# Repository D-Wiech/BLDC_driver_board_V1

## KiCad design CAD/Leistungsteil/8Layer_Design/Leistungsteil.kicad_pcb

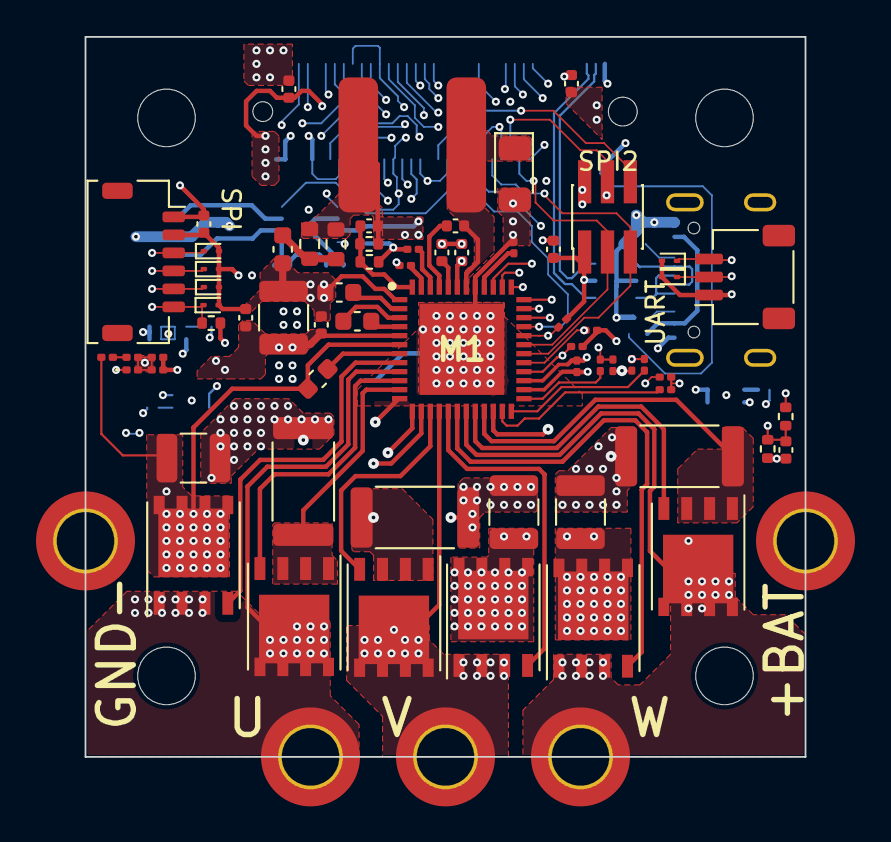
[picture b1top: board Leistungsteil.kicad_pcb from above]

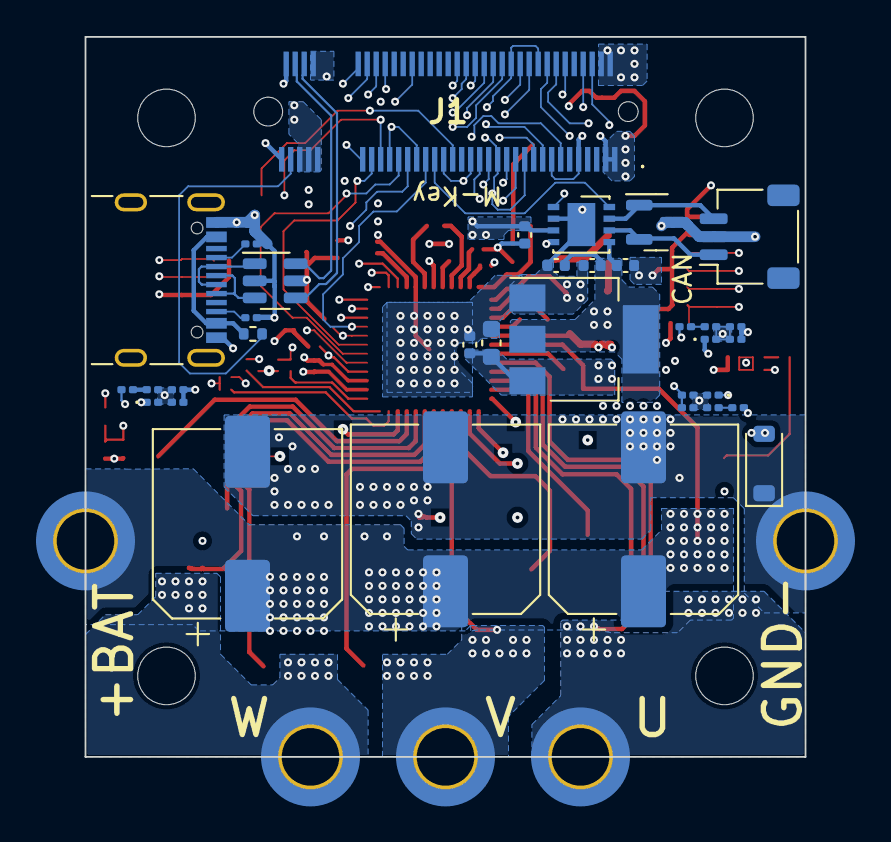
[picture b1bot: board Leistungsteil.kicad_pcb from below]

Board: 8 copper layers, 40.0 x 40.0 mm, 109 parts (35 on the bottom side), 75 nets.

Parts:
CAN_Con1, CAN_Con2: Conn_01x03_Pin; JST_SH_SM03B-SRSS-TB_1x03-1MP_P1.00mm_Horizontal
C_1: 10u; C_1210_3225Metric
C_5V1: 10u; C_0603_1608Metric
C_BST1: 10n; C_0402_1005Metric
C_DVDD1: 1u; C_0201_0603Metric
C_DVDD2: 1u; C_0603_1608Metric
C_FB1: 1n6; C_0402_1005Metric
C_Filter_U1: 1n; C_0201_0603Metric
C_Filter_V1: 1n; C_0201_0603Metric
C_Filter_W1: 1n; C_0201_0603Metric
C_IN1, C_IN2, C_IN3: 100u; CP_Elec_10x10
C_IN4, C_IN5, C_IN6: 10u; C_1210_3225Metric
C_IN7: 100n; C_0402_1005Metric
C_LDO1, C_LDO2, C_LDO6: 22u; C_0402_1005Metric
C_LDO3: 10u; C_0603_1608Metric
C_LDO4, C_LDO5: 100n; C_0402_1005Metric
C_PUMP1: 47n; C_0603_1608Metric
C_Reset1, C_Reset2: 100n; C_0402_1005Metric
C_SENS_Temp1: 100n; C_0402_1005Metric
C_SPI1, C_SPI2: 100n; C_0402_1005Metric
C_VCC1: 470n; C_0402_1005Metric
C_VDRAIN1: 1u; C_0603_1608Metric
C_VM1, C_VM2: 100n; C_0402_1005Metric
C_VM_1: 100n; C_0201_0603Metric
C_Vref1: 1u; C_0201_0603Metric
C_sense_U1: 10n; C_0201_0603Metric
C_sense_V1: 10n; C_0201_0603Metric
C_sense_W1: 10n; C_0201_0603Metric
D1: FES1DE; DO-219AA
D1_ESD1, D1_ESD2, D1_ESD3, D1_ESD4, D1_ESD5, D1_ESD6: ESD9B3.3ST5G; D_SOD-923
D2: PESD1CAN; SOT-23
D_TVS1: SMF54CA; D_SOD-123
D_VBAT1: RB751S-40DP-TP; D_0201_0603Metric
D_sense_U1: RB751S-40DP-TP; D_0201_0603Metric
D_sense_V1: RB751S-40DP-TP; D_0201_0603Metric
D_sense_W1: RB751S-40DP-TP; D_0201_0603Metric
H1, H2, H3, H4: MountingHole; MountingHole_3.2mm_M3_DIN965
J1: Bus_M.2_Socket_M; APCI0110
J7: USB_C_Receptacle_USB2.0; USB_C_Receptacle_GCT_USB4105-xx-A_16P_TopMnt_Horizontal
JST_SPI1: Conn_01x06_Female; JST_SHL_SM06B-SHLS-TF_1x06-1MP_P1.00mm_Horizontal
L1: 470u; NRSE8040-471M
M1: DRV8353RSRGZR; QFN50P700X700X100-49N-D
NTC1: 10k; R_0402_1005Metric
Negativ1: MountingHole_Pad; MountingHole_3.2mm_M3_ISO14580_Pad_TopBottom
Phase_U1: MountingHole_Pad; MountingHole_3.2mm_M3_ISO14580_Pad_TopBottom
Phase_V1: MountingHole_Pad; MountingHole_3.2mm_M3_ISO14580_Pad_TopBottom
Phase_W1: MountingHole_Pad; MountingHole_3.2mm_M3_ISO14580_Pad_TopBottom
Positiv1: MountingHole_Pad; MountingHole_3.2mm_M3_ISO14580_Pad_TopBottom
Q_P_U_H1: SiR584DP; PowerPAK_SO-8_Single
Q_P_U_L1: SiR584DP; PowerPAK_SO-8_Single
Q_P_V_H1: SiR584DP; PowerPAK_SO-8_Single
Q_P_V_L1: SiR584DP; PowerPAK_SO-8_Single
Q_P_W_H1: SiR584DP; PowerPAK_SO-8_Single
Q_P_W_L1: SiR584DP; PowerPAK_SO-8_Single
R_BAT1, R_BAT2: 40k; R_0201_0603Metric
R_CAN1: 3k3; R_0402_1005Metric
R_CS1, R_CS2, R_CS3: 150; R_0201_0603Metric
R_C_s1, R_C_s2: 1,5; R_0603_1608Metric
R_FB1, R_FB2: 10k; R_0402_1005Metric
R_Fault1: 10k; R_0201_0603Metric
R_RCL1: 130k; R_0201_0603Metric
R_RT/SD1: 250k; R_0201_0603Metric
R_SCLK1: 10k; R_0201_0603Metric
R_SDO_PU1: 1k; R_0201_0603Metric
R_SENS_Temp1: 4k7; R_0402_1005Metric
R_USB1, R_USB2: 5k1; R_0201_0603Metric
R_USB3: 1k; R_0402_1005Metric
R_VM_1: 5K; R_0201_0603Metric
R_sense_U1, R_sense_U3: 40k; R_0201_0603Metric
R_sense_U2: 5K; R_0201_0603Metric
R_sense_V1, R_sense_V2: 40k; R_0201_0603Metric
R_sense_V3: 5K; R_0201_0603Metric
R_sense_W1, R_sense_W2: 40k; R_0201_0603Metric
R_sense_W3: 5K; R_0201_0603Metric
Rs_P_U1: 5m; R_2512_6332Metric
Rs_P_V1: 5m; R_2512_6332Metric
Rs_P_W1: 5m; R_2512_6332Metric
SPI2: Conn_01x06_Female; PinHeader_2x03_P1.27mm_Vertical_SMD
U1: LDL1117; SOT-223-3_TabPin2
U2: USBLC6-2SC6; SOT-23-6
U3: SIT1042QTK/3; DFN-8-1EP_3x3mm_P0.65mm_EP1.55x2.4mm

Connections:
+3V3: C_LDO1.1, C_LDO2.1, C_LDO5.1, C_LDO6.1, C_Reset1.1, C_SPI1.1, C_SPI2.1, C_Vref1.1, D_VBAT1.1 (K), D_sense_U1.1 (K), D_sense_V1.1 (K), D_sense_W1.1 (K), J1.2 (3.3V), J1.4 (3.3V), J1.67 (3.3V), J1.69 (3.3V), J1.71 (3.3V), JST_SPI1.1, M1.26 (VREF), NTC1.1, R_CAN1.1, R_Fault1.2, R_SCLK1.2, R_SDO_PU1.2, SPI2.1, U1.2 (VO), U2.5 (VBUS), U3.5 (VIO)
+5V: C_FB1.1, C_LDO3.1, C_LDO4.1, C_Reset2.1, L1.1, R_C_s1.2, R_C_s2.2, R_FB1.2, U1.3 (VI), U3.3 (VCC)
+BATT: C_1.2, C_IN1.1, C_IN2.1, C_IN3.1, C_IN4.2, C_IN5.2, C_IN6.2, C_IN7.2, C_VDRAIN1.1, C_VM1.1, C_VM2.1, D_TVS1.2 (A2), M1.5 (VM), M1.6 (VDRAIN), M1.43 (VIN), Positiv1.1, Q_P_U_H1.5 (D), Q_P_V_H1.5 (D), Q_P_W_H1.5 (D), R_BAT1.1, R_RT/SD1.2
/Spannungsversorgung/CC1: J7.A5 (CC1), R_USB2.1
/Spannungsversorgung/CC2: J7.B5 (CC2), R_USB1.1
ADC1_3: C_sense_V1.1, D_sense_V1.2 (A), J1.6 (Analog4_2), R_sense_V2.2, R_sense_V3.1
ADC1_+: C_Filter_V1.1, J1.17 (Analog1_2), R_CS2.2
ADC1_-: C_Filter_U1.1, J1.19 (Analog1_1), R_CS1.2
ADC2_3: C_sense_W1.1, D_sense_W1.2 (A), J1.8 (Analog4_3), R_sense_W2.2, R_sense_W3.1
ADC2_-: C_Filter_W1.1, J1.13 (Analog2_1), R_CS3.2
ADC3_1: C_VM_1.1, D_VBAT1.2 (A), J1.14 (Analog4_6), R_BAT2.2, R_VM_1.1
ADC3_2: C_SENS_Temp1.1, J1.12 (Analog4_5), NTC1.2, R_SENS_Temp1.1
ADC321_4: C_sense_U1.1, D_sense_U1.2 (A), J1.16 (Analog4_1), R_sense_U1.2, R_sense_U2.1
CAN_RX: J1.22 (CAN_1), U3.4 (RXD)
CAN_TX: J1.20 (CAN_2), U3.1 (TXD)
I2C_SCL: J1.41 (I2C1_2), U3.8 (STB)
I2C_SDA: J1.43 (I2C1_1), M1.33 (ENABLE)
LPUART RX: CAN_Con2.3, D1_ESD6.1 (K), J1.56 (UART2_1)
LPUART TX: CAN_Con2.2, D1_ESD5.1 (K), J1.58 (UART2_2)
unnamed: CAN_Con1.1, D2.2 (K), U3.6 (CANL)
unnamed: CAN_Con1.3, D2.1 (K), U3.7 (CANH)
unnamed: C_5V1.1, R_C_s1.1, R_C_s2.1
unnamed: C_BST1.1, D1.1 (K), L1.2, M1.42 (SW)
unnamed: J7.A4 (VBUS), J7.A9 (VBUS), J7.B4 (VBUS), J7.B9 (VBUS), R_USB3.1
unnamed: C_BST1.2, M1.45 (BST)
unnamed: C_PUMP1.2, M1.4 (CPH)
unnamed: C_PUMP1.1, M1.3 (CPL)
unnamed: C_DVDD1.1, M1.40 (DVDD)
unnamed: C_FB1.2, M1.48 (FB), R_FB1.1, R_FB2.2
unnamed: M1.46 (RCL), R_RCL1.1
unnamed: M1.47 (RT/SD), R_RT/SD1.1
unnamed: M1.25 (SOA), R_CS1.1
unnamed: M1.24 (SOB), R_CS2.1
unnamed: M1.23 (SOC), R_CS3.1
unnamed: C_VCC1.1, M1.44 (VCC)
unnamed: C_VDRAIN1.2, M1.7 (VCP)
unnamed: C_DVDD2.1, M1.2 (VGLS)
unnamed: R_BAT1.2, R_BAT2.1
unnamed: R_sense_U1.1, R_sense_U3.2
unnamed: R_sense_V1.2, R_sense_V2.1
unnamed: R_sense_W1.2, R_sense_W2.1
PWM_U_N: J1.26 (PWM1_2), M1.35 (INLA)
PWM_U_P: J1.28 (PWM1_1), M1.34 (INHA)
PWM_V_N: J1.30 (PWM2_2), M1.37 (INLB)
PWM_V_P: J1.32 (PWM2_1), M1.36 (INHB)
PWM_W_N: J1.34 (PWM3_2), M1.39 (INLC)
PWM_W_P: J1.36 (PWM3_1), M1.38 (INHC)
Phase_U_GND: CAN_Con1.2, CAN_Con2.1, C_1.1, C_5V1.2, C_DVDD1.2, C_DVDD2.2, C_Filter_U1.2, C_Filter_V1.2, C_Filter_W1.2, C_IN1.2, C_IN2.2, C_IN3.2, C_IN4.1, C_IN5.1, C_IN6.1, C_IN7.1, C_LDO1.2, C_LDO2.2, C_LDO3.2, C_LDO4.2, C_LDO5.2, C_LDO6.2, C_Reset1.2, C_Reset2.2, C_SENS_Temp1.2, C_SPI1.2, C_SPI2.2, C_VCC1.2, C_VM1.2, C_VM2.2, C_VM_1.2, C_Vref1.2, C_sense_U1.2, C_sense_V1.2, C_sense_W1.2, D1.2 (A), D1_ESD1.2 (A), D1_ESD2.2 (A), D1_ESD3.2 (A), D1_ESD4.2 (A), D1_ESD5.2 (A), D1_ESD6.2 (A), D2.3 (A), D_TVS1.1 (A1), J1.1 (GND), J1.3 (GND), J1.9 (GND), J1.15 (GND), J1.18 (GND), J1.21 (GND), J1.24 (GND), J1.27 (GND), J1.33 (GND), J1.39 (GND), J1.45 (GND), J1.46 (GND), J1.51 (GND), J1.54 (GND), J1.57 (GND), J1.68 (GND), J1.74 (GND), J1.75 (GND), J7.A1 (GND), J7.A12 (GND), J7.B1 (GND), J7.B12 (GND), JST_SPI1.2, M1.1 (GND), M1.12 (SNA), M1.13 (SNB), M1.22 (SNC), M1.27 (AGND), M1.41 (DGND), M1.49 (PAD), Negativ1.1, R_FB2.1, R_RCL1.2, R_SENS_Temp1.2, R_USB1.2, R_USB2.2, R_VM_1.2, R_sense_U2.2, R_sense_V3.2, R_sense_W3.2, Rs_P_U1.1, Rs_P_V1.1, Rs_P_W1.1, SPI2.2, U1.1 (GND), U2.2 (GND), U3.2 (GND), U3.9 (GND)
Phase_U_Gate_H: M1.8 (GHA), Q_P_U_H1.4 (G)
Phase_U_Gate_L: M1.10 (GLA), Q_P_U_L1.4 (G)
Phase_U_Source_H: M1.9 (SHA), Phase_U1.1, Q_P_U_H1.1 (S), Q_P_U_H1.2 (S), Q_P_U_H1.3 (S), Q_P_U_L1.5 (D), R_sense_U3.1
Phase_U_Source_L: M1.11 (SPA), Q_P_U_L1.1 (S), Q_P_U_L1.2 (S), Q_P_U_L1.3 (S), Rs_P_U1.2
Phase_V_Gate_H: M1.17 (GHB), Q_P_V_H1.4 (G)
Phase_V_Gate_L: M1.15 (GLB), Q_P_V_L1.4 (G)
Phase_V_Source_H: M1.16 (SHB), Phase_V1.1, Q_P_V_H1.1 (S), Q_P_V_H1.2 (S), Q_P_V_H1.3 (S), Q_P_V_L1.5 (D), R_sense_V1.1
Phase_V_Source_L: M1.14 (SPB), Q_P_V_L1.1 (S), Q_P_V_L1.2 (S), Q_P_V_L1.3 (S), Rs_P_V1.2
Phase_W_Gate_H: M1.18 (GHC), Q_P_W_H1.4 (G)
Phase_W_Gate_L: M1.20 (GLC), Q_P_W_L1.4 (G)
Phase_W_Source_H: M1.19 (SHC), Phase_W1.1, Q_P_W_H1.1 (S), Q_P_W_H1.2 (S), Q_P_W_H1.3 (S), Q_P_W_L1.5 (D), R_sense_W1.1
Phase_W_Source_L: M1.21 (SPC), Q_P_W_L1.1 (S), Q_P_W_L1.2 (S), Q_P_W_L1.3 (S), Rs_P_W1.2
SPI_1_CS: D1_ESD4.1 (K), J1.23 (SPI2_2), JST_SPI1.6, R_CAN1.2
SPI_1_MISO: D1_ESD3.1 (K), J1.29 (SPI2_4), JST_SPI1.5
SPI_1_MOSI: D1_ESD1.1 (K), J1.31 (SPI2_3), JST_SPI1.3
SPI_1_SCLK: D1_ESD2.1 (K), J1.25 (SPI2_1), JST_SPI1.4
SPI_2_CS: J1.47 (SPI1_3), M1.32 (NSCS), R_SCLK1.1
SPI_2_MISO: J1.53 (SPI1_2), M1.29 (SDO), R_SDO_PU1.1, SPI2.4
SPI_2_MOSI: J1.49 (SPI1_4), M1.30 (SDI), SPI2.5
SPI_2_SCLK: J1.55 (SPI1_1), M1.31 (SCLK), SPI2.3
TIM1_BKIN: J1.52 (I2C2_3), M1.28 (NFAULT), R_Fault1.1
UART8_TX: J1.37 (UART1_2), SPI2.6
USB_CONN_D+: J7.A6 (D+), J7.B6 (D+), U2.3 (I/O2)
USB_CONN_D-: J7.A7 (D-), J7.B7 (D-), U2.1 (I/O1)
USB_D+: J1.70 (USB_D+), U2.4 (I/O2)
USB_D-: J1.72 (USB_D-), U2.6 (I/O1)
USB_Spannung: J1.73 (USB_Detect), R_USB3.2

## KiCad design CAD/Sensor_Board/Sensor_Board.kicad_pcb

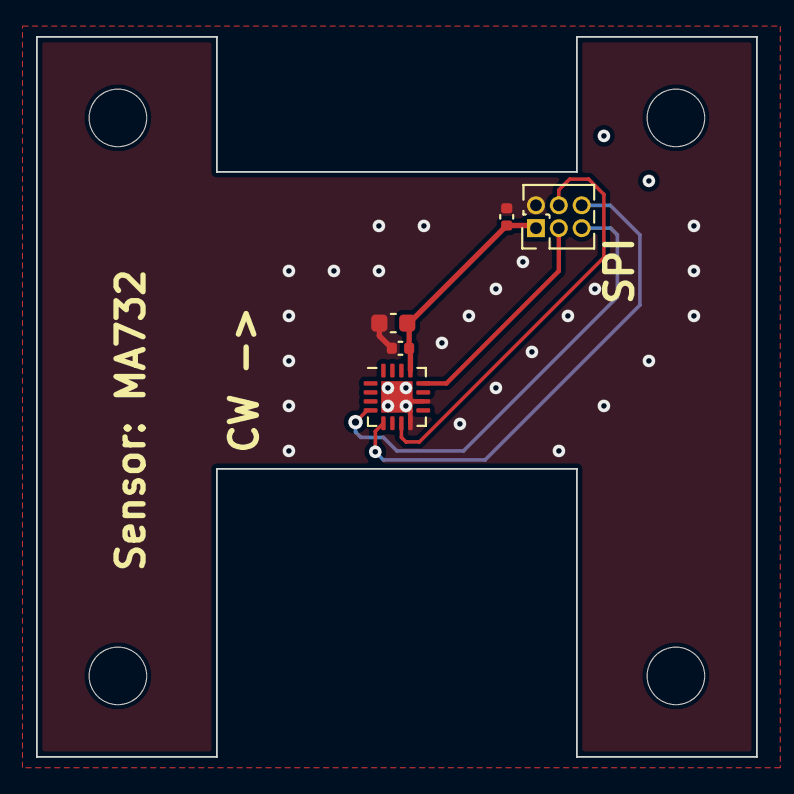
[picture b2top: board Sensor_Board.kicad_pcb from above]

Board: 2 copper layers, 40.0 x 40.0 mm, 9 parts (0 on the bottom side), 6 nets.

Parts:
C_SENS1, C_SENS2: 100n; C_0402_1005Metric
C_SENS4: 1u; C_0603_1608Metric
H1, H2, H3, H4: M3; MountingHole_3.2mm_M3_DIN965
JST_SENS1: Conn_01x06_Female; PinHeader_2x03_P1.27mm_Vertical
U1: MA730; QFN-16-1EP_3x3mm_P0.5mm_EP1.75x1.75mm

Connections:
+3V3: C_SENS1.1, C_SENS2.1, C_SENS4.1, JST_SENS1.1, U1.13 (VDD)
GNDD: C_SENS1.2, C_SENS2.2, C_SENS4.2, JST_SENS1.2, U1.8 (GND), U1.10 (TEST), U1.17 (PAD)
SENS_SPI_CS: JST_SENS1.6, U1.5 (~CS)
SENS_SPI_MISO: JST_SENS1.4, U1.7 (MISO)
SENS_SPI_MOSI: JST_SENS1.5, U1.4 (MOSI)
SENS_SPI_SCLK: JST_SENS1.3, U1.12 (SCLK)

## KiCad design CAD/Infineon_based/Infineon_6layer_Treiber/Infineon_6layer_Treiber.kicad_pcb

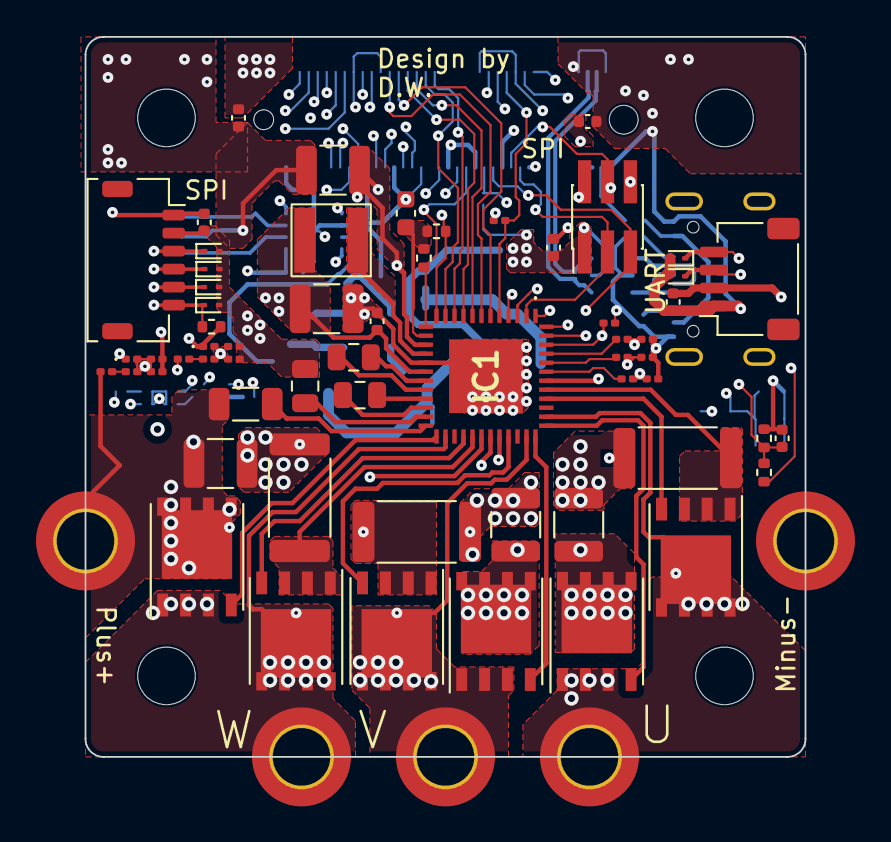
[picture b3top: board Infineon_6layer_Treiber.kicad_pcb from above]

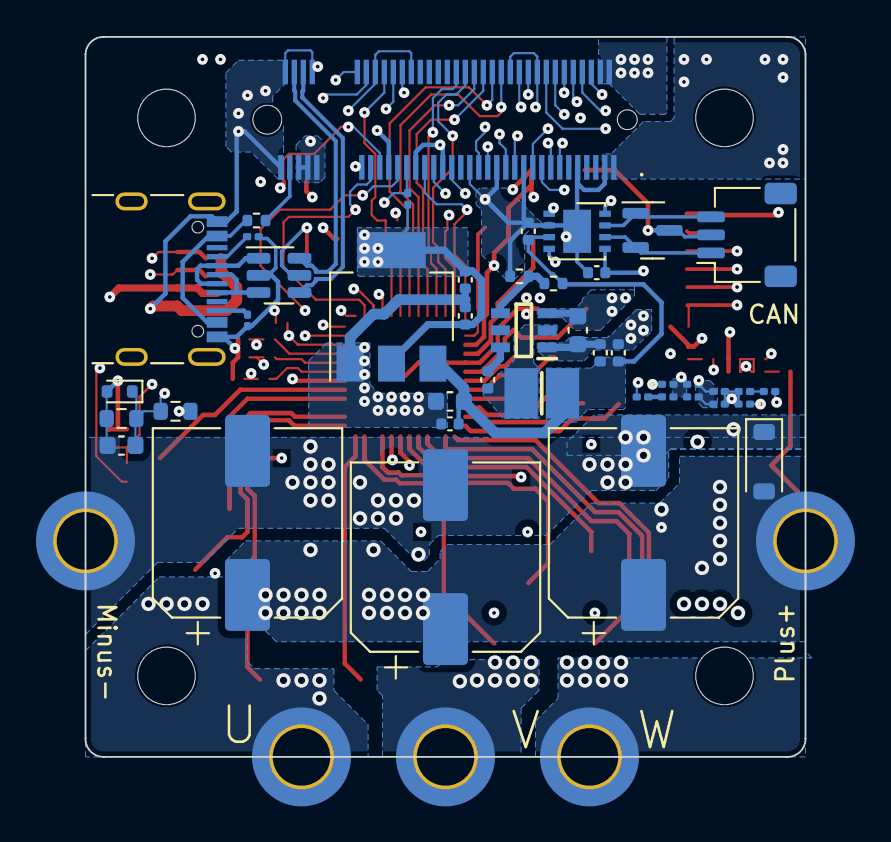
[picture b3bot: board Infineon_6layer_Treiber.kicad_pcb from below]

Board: 6 copper layers, 40.0 x 40.0 mm, 112 parts (43 on the bottom side), 79 nets.

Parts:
CAN_Con2: Conn_01x03_Pin; JST_SH_SM03B-SRSS-TB_1x03-1MP_P1.00mm_Horizontal
C_Buck1: 47u; C_1210_3225Metric
C_Buck2: 100n; C_0402_1005Metric
C_CE1: 100n; C_0603_1608Metric
C_DVDD1: 22u; C_0603_1608Metric
C_IN1, C_IN2, C_IN3: 100u; CP_Elec_10x10
C_IN4, C_IN5, C_IN6: 10u; C_1210_3225Metric
C_I_U1: 1n; C_0201_0603Metric
C_I_V1: 1n; C_0201_0603Metric
C_I_W1: 1n; C_0201_0603Metric
C_LDO1: 10u; C_0603_1608Metric
C_LDO2, C_LDO3: 100n; C_0402_1005Metric
C_LDO4, C_LDO5, C_LDO6: 22u; C_0402_1005Metric
C_PVDD1: 10u; C_1210_3225Metric
C_Reset1, C_Reset2: 100n; C_0402_1005Metric
C_SENS_Temp1: 100n; C_0402_1005Metric
C_SPI1, C_SPI2, C_SPI3: 100n; C_0402_1005Metric
C_VCCLS1: 4u7; C_0805_2012Metric
C_VCCLS2: 2u2; C_1206_3216Metric
C_VM_1: 100n; C_0201_0603Metric
C_VM_2, C_VM_3, C_VM_4: 10n; C_0201_0603Metric
C_VREF2: 100n; C_0402_1005Metric
C_VREF3: 10u 25V; C_0603_1608Metric
C_VREF4, C_VREF5: 22u 6V; C_0402_1005Metric
C_VRef1: 100n; C_0201_0603Metric
D1: PESD1CAN; SOT-23
D1_ESD1, D1_ESD2, D1_ESD3, D1_ESD4, D1_ESD5, D1_ESD6: ESD9B3.3ST5G; D_SOD-923
D2: BZT52C4V7T-7; D_SOD-523
D_TVS1: SMF54CA; D_SOD-123
D_VBAT1, D_VBAT2, D_VBAT3, D_VBAT4: RB751S-40DP-TP; D_0201_0603Metric
H1, H2, H3, H4: MountingHole; MountingHole_3.2mm_M3_ISO14580
I2C1: Conn_01x04_Pin; JST_SH_SM04B-SRSS-TB_1x04-1MP_P1.00mm_Horizontal
IC1: 6EDL7141XUMA1
IC2: AP62200WU-7; SOT95P280X100-6N
J1: Plus; MountingHole_3.2mm_M3_ISO14580_Pad_TopBottom
J2: Minus; MountingHole_3.2mm_M3_ISO14580_Pad_TopBottom
J3: U; MountingHole_3.2mm_M3_ISO14580_Pad_TopBottom
J4: V; MountingHole_3.2mm_M3_ISO14580_Pad_TopBottom
J5: W; MountingHole_3.2mm_M3_ISO14580_Pad_TopBottom
J6: USB_C_Receptacle_USB2.0; USB_C_Receptacle_GCT_USB4105-xx-A_16P_TopMnt_Horizontal
J7: Bus_M.2_Socket_M; APCI0110
JST_SPI1: Conn_01x06_Female; PinHeader_2x03_P1.27mm_Vertical_SMD
JST_SPI2: Conn_01x06_Female; JST_SHL_SM06B-SHLS-TF_1x06-1MP_P1.00mm_Horizontal
L2: SRP3212A-3R3M; INDC3225X120N
L_Buck1: 22u; MPL-SE4030-220
Ladungspumpe1: 470nF; C_0805_2012Metric
Ladungspumpe2: 470nF 100V; C_0805_2012Metric
NTC1: 10k; R_0402_1005Metric
Q_P_U_H1: SiR584DP; PowerPAK_SO-8_Single
Q_P_U_L1: SiR584DP; PowerPAK_SO-8_Single
Q_P_V_H1: SiR584DP; PowerPAK_SO-8_Single
Q_P_V_L1: SiR584DP; PowerPAK_SO-8_Single
Q_P_W_H1: SiR584DP; PowerPAK_SO-8_Single
Q_P_W_L1: SiR584DP; PowerPAK_SO-8_Single
R_BAT1, R_BAT2, R_BAT3, R_BAT4, R_BAT5, R_BAT6, R_BAT7, R_BAT8: 40k; R_0201_0603Metric
R_BAT9: 52k3; R_0402_1005Metric
R_BAT10: 10k; R_0402_1005Metric
R_Brake1: 3k3; R_0402_1005Metric
R_CAN1: 3k3; R_0402_1005Metric
R_CAN2: 1k; R_0402_1005Metric
R_CE1, R_CE2: 30k; R_0603_1608Metric
R_CS1: 10k; R_0201_0603Metric
R_Fault1: 10k; R_0201_0603Metric
R_I_U1: 150; R_0201_0603Metric
R_I_V1: 150; R_0201_0603Metric
R_I_W1: 150; R_0201_0603Metric
R_SENS_Temp1: 4k7; R_0402_1005Metric
R_USB1, R_USB2: 5k1; R_0201_0603Metric
R_VM_1, R_VM_2, R_VM_3, R_VM_4: 5K; R_0201_0603Metric
R_Warning1: 10k; R_0402_1005Metric
Rs_P_U1: 5m; R_2512_6332Metric
Rs_P_V1: 5m; R_2512_6332Metric
Rs_P_W1: 5m; R_2512_6332Metric
U1: USBLC6-2SC6; SOT-23-6
U2: SIT1042QTK/3; DFN-8-1EP_3x3mm_P0.65mm_EP1.55x2.4mm
U3: LDL1117; SOT-223-3_TabPin2

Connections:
3V3: C_LDO3.1, C_LDO4.1, C_LDO5.1, C_LDO6.1, C_Reset1.1, C_SPI1.1, C_SPI2.1, C_SPI3.1, D_VBAT1.1 (K), D_VBAT2.1 (K), D_VBAT3.1 (K), D_VBAT4.1 (K), I2C1.2, J7.2 (3.3V), J7.4 (3.3V), J7.67 (3.3V), J7.69 (3.3V), J7.71 (3.3V), JST_SPI1.1, JST_SPI2.1, NTC1.1, R_CAN1.1, R_CS1.2, R_Fault1.2, U1.5 (VBUS), U2.5 (VIO), U3.2 (VO)
+5V: C_LDO1.1, C_LDO2.1, C_Reset2.1, C_VREF4.2, C_VREF5.2, L2.2, R_BAT9.1, U2.3 (VCC), U3.3 (VI)
+BATT: C_IN1.1, C_IN2.1, C_IN3.1, C_IN4.2, C_IN5.2, C_IN6.2, C_PVDD1.2, C_VCCLS2.1, D_TVS1.2 (A2), IC1.15 (PVDD), J1.1, Q_P_U_H1.5 (D), Q_P_V_H1.5 (D), Q_P_W_H1.5 (D), R_BAT1.1, R_CE1.1
/Spannungsversorgung_usw/BST: C_VREF2.2, IC2.6 (BST)
/Spannungsversorgung_usw/CC1: J6.A5 (CC1), R_USB2.1
/Spannungsversorgung_usw/CC2: J6.B5 (CC2), R_USB1.1
/Spannungsversorgung_usw/FB: IC2.4 (FB), R_BAT9.2, R_BAT10.1
/Spannungsversorgung_usw/SW: C_VREF2.1, IC2.2 (SW), L2.1
/Treiber/DVDD (3V3): C_DVDD1.1, IC1.14 (DVDD), R_Brake1.2, R_Warning1.2
ADC1_3: C_VM_3.1, D_VBAT3.2 (A), J7.6 (Analog4_2), R_BAT6.2, R_VM_3.1
ADC1_+: C_I_V1.1, J7.17 (Analog1_2), R_I_V1.2
ADC1_-: C_I_U1.1, J7.19 (Analog1_1), R_I_U1.2
ADC2_3: C_VM_4.1, D_VBAT4.2 (A), J7.8 (Analog4_3), R_BAT8.2, R_VM_4.1
ADC2_-: C_I_W1.1, J7.13 (Analog2_1), R_I_W1.2
ADC3_1: C_VM_1.1, D_VBAT1.2 (A), J7.14 (Analog4_6), R_BAT2.2, R_VM_1.1
ADC3_2: C_SENS_Temp1.1, J7.12 (Analog4_5), NTC1.2, R_SENS_Temp1.1
ADC321_4: C_VM_2.1, D_VBAT2.2 (A), J7.16 (Analog4_1), R_BAT4.2, R_VM_2.1
CAN_RX: J7.22 (CAN_1), U2.4 (RXD)
CAN_TX: J7.20 (CAN_2), U2.1 (TXD)
DAC_OUT: C_VRef1.1, IC1.46 (VREF), J7.10 (Analog4_4)
ENABLE: C_CE1.1, D2.1 (K), IC1.47 (CE), R_CE1.2, R_CE2.1
I2C2_SCL: IC1.12 (CS_GAIN/_AZ), J7.50 (I2C2_2), R_Warning1.1
I2C2_SDA: IC1.48 (EN_DRV), J7.48 (I2C2_1)
I2C_SCL: J7.41 (I2C1_2), U2.8 (STB)
I2C_SDA: IC1.13 (VSENSE/_NBRAKE), J7.43 (I2C1_1), R_Brake1.1
LPUART RX: D1_ESD1.1 (K), I2C1.4, J7.56 (UART2_1)
LPUART TX: D1_ESD2.1 (K), I2C1.3, J7.58 (UART2_2)
unnamed: CAN_Con2.1, D1.2 (K), U2.6 (CANL)
unnamed: CAN_Con2.3, D1.1 (K), U2.7 (CANH)
unnamed: IC1.20 (CP1H), Ladungspumpe1.2
unnamed: IC1.19 (CP1L), Ladungspumpe1.1
unnamed: IC1.22 (CP2H), Ladungspumpe2.2
unnamed: IC1.21 (CP2L), Ladungspumpe2.1
unnamed: IC1.43 (CSOA), R_I_U1.1
unnamed: IC1.44 (CSOB), R_I_V1.1
unnamed: IC1.45 (CSOC), R_I_W1.1
unnamed: C_VCCLS2.2, IC1.24 (VCCHS)
unnamed: C_VCCLS1.2, IC1.23 (VCCLS)
unnamed: J6.A4 (VBUS), J6.A9 (VBUS), J6.B4 (VBUS), J6.B9 (VBUS), R_CAN2.1
unnamed: R_BAT1.2, R_BAT2.1
unnamed: R_BAT3.2, R_BAT4.1
unnamed: R_BAT5.2, R_BAT6.1
unnamed: R_BAT7.2, R_BAT8.1
OUT_U: IC1.38 (SHA), J3.1, Q_P_U_H1.1 (S), Q_P_U_H1.2 (S), Q_P_U_H1.3 (S), Q_P_U_L1.5 (D), R_BAT3.1
OUT_V: IC1.35 (SHB), J4.1, Q_P_V_H1.1 (S), Q_P_V_H1.2 (S), Q_P_V_H1.3 (S), Q_P_V_L1.5 (D), R_BAT5.1
OUT_W: IC1.26 (SHC), J5.1, Q_P_W_H1.1 (S), Q_P_W_H1.2 (S), Q_P_W_H1.3 (S), Q_P_W_L1.5 (D), R_BAT7.1
PH: IC1.16 (PH), L_Buck1.1
PWM_U_N: IC1.7 (INLA), J7.26 (PWM1_2)
PWM_U_P: IC1.6 (INHA), J7.28 (PWM1_1)
PWM_V_N: IC1.9 (INLB), J7.30 (PWM2_2)
PWM_V_P: IC1.8 (INHB), J7.32 (PWM2_1)
PWM_W_N: IC1.11 (INLC), J7.34 (PWM3_2)
PWM_W_P: IC1.10 (INHC), J7.36 (PWM3_1)
Phase_U_GND: CAN_Con2.2, C_Buck1.1, C_Buck2.1, C_CE1.2, C_DVDD1.2, C_IN1.2, C_IN2.2, C_IN3.2, C_IN4.1, C_IN5.1, C_IN6.1, C_I_U1.2, C_I_V1.2, C_I_W1.2, C_LDO1.2, C_LDO2.2, C_LDO3.2, C_LDO4.2, C_LDO5.2, C_LDO6.2, C_PVDD1.1, C_Reset1.2, C_Reset2.2, C_SENS_Temp1.2, C_SPI1.2, C_SPI2.2, C_SPI3.2, C_VCCLS1.1, C_VM_1.2, C_VM_2.2, C_VM_3.2, C_VM_4.2, C_VREF3.1, C_VREF4.1, C_VREF5.1, C_VRef1.2, D1.3 (A), D1_ESD1.2 (A), D1_ESD2.2 (A), D1_ESD3.2 (A), D1_ESD4.2 (A), D1_ESD5.2 (A), D1_ESD6.2 (A), D2.2 (A), D_TVS1.1 (A1), I2C1.1, IC1.17 (PGND), IC1.30 (CSNC), IC1.31 (CSNB), IC1.42 (CSNA), IC1.49 (DGND), IC2.1 (GND), J2.1, J6.A1 (GND), J6.A12 (GND), J6.B1 (GND), J6.B12 (GND), J7.1 (GND), J7.3 (GND), J7.9 (GND), J7.15 (GND), J7.18 (GND), J7.21 (GND), J7.24 (GND), J7.27 (GND), J7.33 (GND), J7.39 (GND), J7.45 (GND), J7.46 (GND), J7.51 (GND), J7.54 (GND), J7.57 (GND), J7.68 (GND), J7.74 (GND), J7.75 (GND), JST_SPI1.2, JST_SPI2.2, R_BAT10.2, R_CE2.2, R_SENS_Temp1.2, R_USB1.2, R_USB2.2, R_VM_1.2, R_VM_2.2, R_VM_3.2, R_VM_4.2, Rs_P_U1.1, Rs_P_V1.1, Rs_P_W1.1, U1.2 (GND), U2.2 (GND), U2.9 (GND), U3.1 (GND)
Phase_U_Gate_H: IC1.37 (GHA), Q_P_U_H1.4 (G)
Phase_U_Gate_L: IC1.40 (GLA), Q_P_U_L1.4 (G)
Phase_U_Source_L: IC1.41 (SLA), Q_P_U_L1.1 (S), Q_P_U_L1.2 (S), Q_P_U_L1.3 (S), Rs_P_U1.2
Phase_V_Gate_H: IC1.36 (GHB), Q_P_V_H1.4 (G)
Phase_V_Gate_L: IC1.33 (GLB), Q_P_V_L1.4 (G)
Phase_V_Source_L: IC1.32 (SLB), Q_P_V_L1.1 (S), Q_P_V_L1.2 (S), Q_P_V_L1.3 (S), Rs_P_V1.2
Phase_W_Gate_H: IC1.25 (GHC), Q_P_W_H1.4 (G)
Phase_W_Gate_L: IC1.28 (GLC), Q_P_W_L1.4 (G)
Phase_W_Source_L: IC1.29 (SLC), Q_P_W_L1.1 (S), Q_P_W_L1.2 (S), Q_P_W_L1.3 (S), Rs_P_W1.2
SPI_1_CS: D1_ESD6.1 (K), J7.23 (SPI2_2), JST_SPI2.6, R_CAN1.2
SPI_1_MISO: D1_ESD5.1 (K), J7.29 (SPI2_4), JST_SPI2.5
SPI_1_MOSI: D1_ESD3.1 (K), J7.31 (SPI2_3), JST_SPI2.3
SPI_1_SCLK: D1_ESD4.1 (K), J7.25 (SPI2_1), JST_SPI2.4
SPI_2_CS: IC1.1 (NSCS), J7.47 (SPI1_3), R_CS1.1
SPI_2_MISO: IC1.3 (SDO), J7.53 (SPI1_2), JST_SPI1.4
SPI_2_MOSI: IC1.4 (SDI), J7.49 (SPI1_4), JST_SPI1.5
SPI_2_SCLK: IC1.2 (SCLK), J7.55 (SPI1_1), JST_SPI1.3
TIM1_BKIN: IC1.5 (NFAULT), J7.52 (I2C2_3), R_Fault1.1
UART8_TX: J7.37 (UART1_2), JST_SPI1.6
USB_CONN_D+: J6.A6 (D+), J6.B6 (D+), U1.3 (I/O2)
USB_CONN_D-: J6.A7 (D-), J6.B7 (D-), U1.1 (I/O1)
USB_D+: J7.70 (USB_D+), U1.4 (I/O2)
USB_D-: J7.72 (USB_D-), U1.6 (I/O1)
USB_Spannung: J7.73 (USB_Detect), R_CAN2.2
VDDB: C_Buck1.2, C_Buck2.2, C_VREF3.2, IC1.18 (VDDB), IC2.3 (VIN), L_Buck1.2

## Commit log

2023-10-29 Initial git setup from existing project
